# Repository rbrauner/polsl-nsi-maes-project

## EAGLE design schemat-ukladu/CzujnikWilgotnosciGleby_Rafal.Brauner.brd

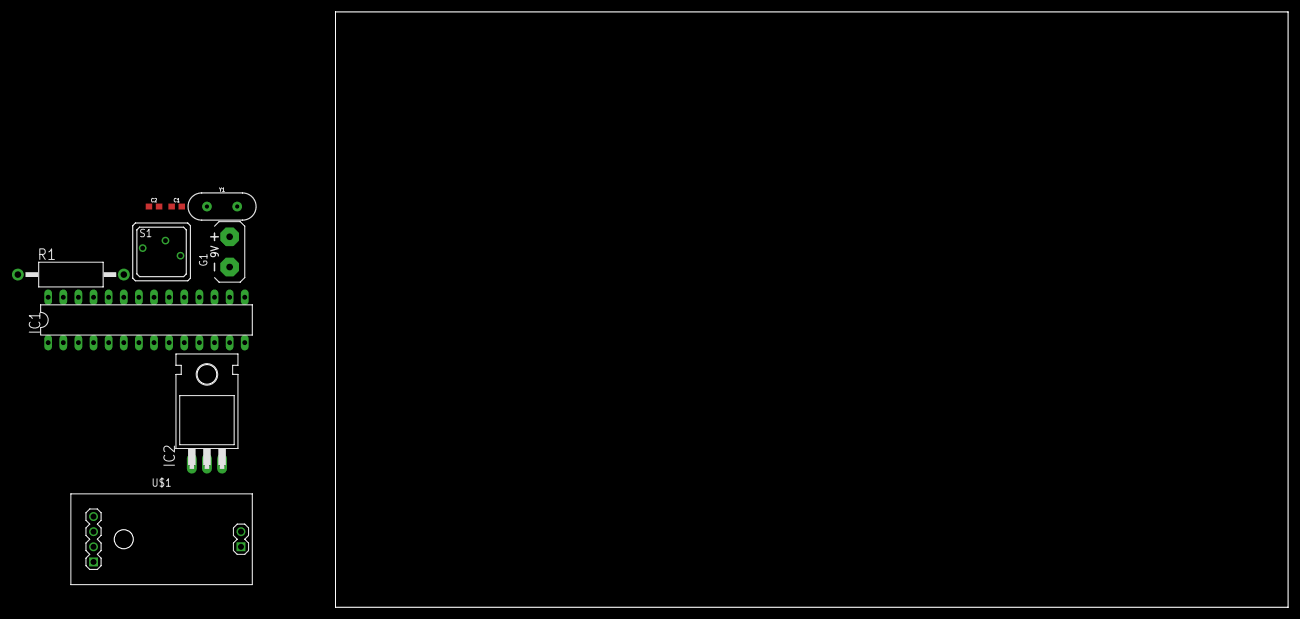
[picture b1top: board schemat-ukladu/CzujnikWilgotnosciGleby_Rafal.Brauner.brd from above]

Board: 2 copper layers, 160.0 x 100.0 mm, 9 parts (0 on the bottom side), 8 nets, no tracks yet.

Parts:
C1, C2: 100pF; 0603
G1: AB9V
IC1: ATMEGA328-20P; DIL28-3
IC2: LM1117T(H)-5.0; TO220H
R1: 100k; AC01
S1: RDT1034
U$1: SOIL-MOISTURE-SENSOR
Y1: HC49US

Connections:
unnamed: G1.+, IC2.3
unnamed: C1.2, IC1.7, IC1.20, IC2.2, R1.2, U$1.J1.4
unnamed: IC1.1, S1.A1
unnamed: R1.1, S1.B
unnamed: C1.1, IC1.9, Y1.2
unnamed: C2.2, G1.-, IC1.8, IC1.22, IC2.1, U$1.J1.3
unnamed: C2.1, IC1.10, Y1.1
unnamed: IC1.28, U$1.J1.1

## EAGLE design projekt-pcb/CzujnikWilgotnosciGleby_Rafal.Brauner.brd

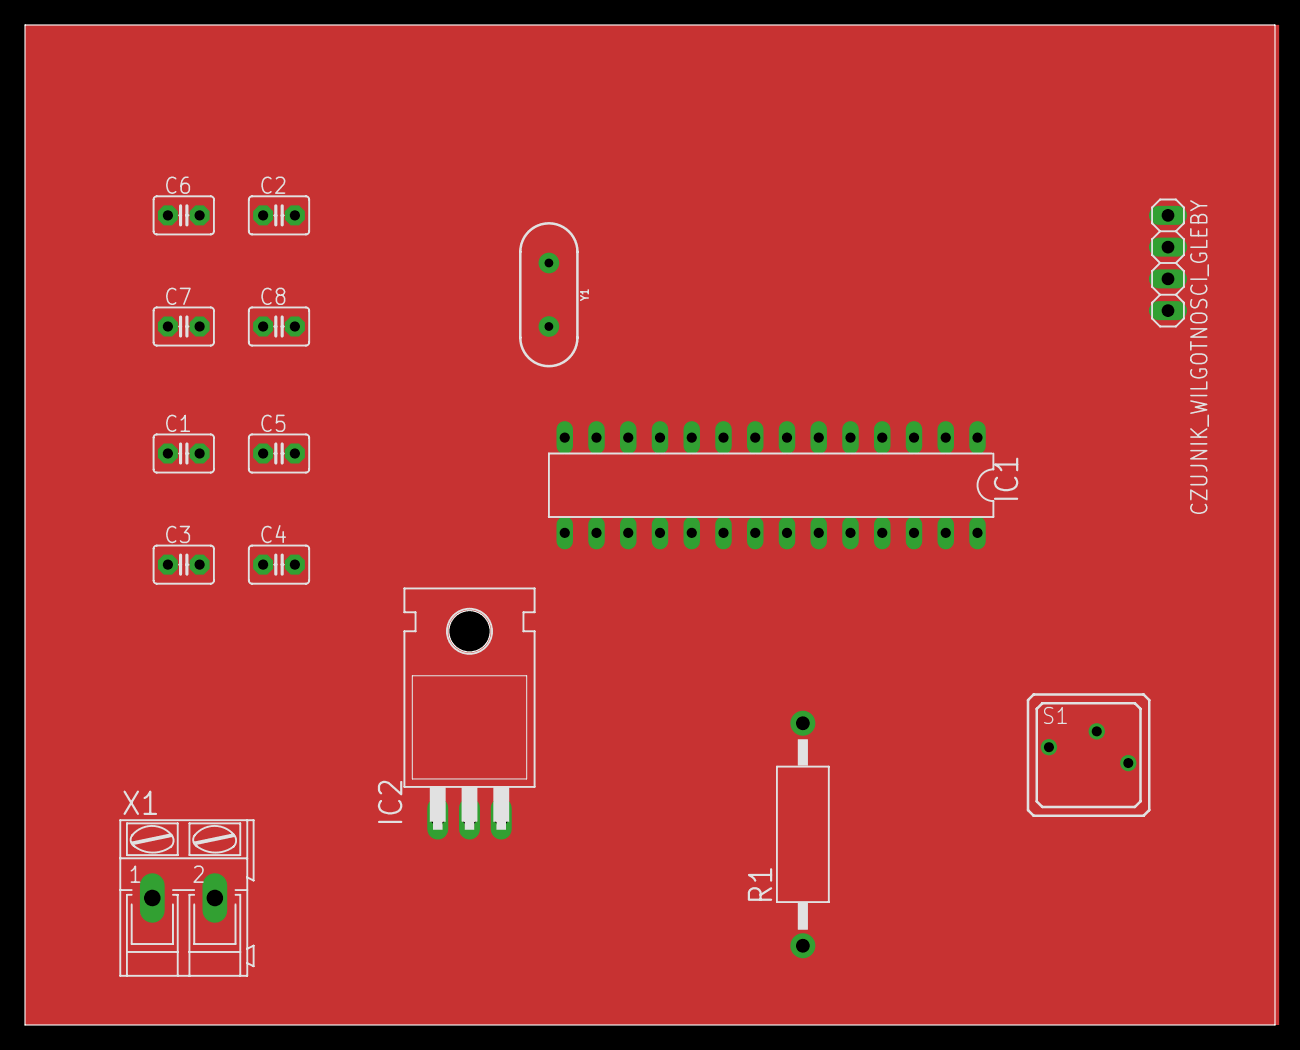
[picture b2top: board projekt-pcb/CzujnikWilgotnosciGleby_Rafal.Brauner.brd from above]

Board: 2 copper layers, 100.0 x 80.0 mm, 15 parts (0 on the bottom side), 9 nets.

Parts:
C1, C2, C3, C4, C6, C7, C8: 100nF; C2.5-3
C5: 22nF; C2.5-3
CZUJNIK_WILGOTNOSCI_GLEBY: 1X04
IC1: ATMEGA328-20P; DIL28-3
IC2: LM1117T(H)-5.0; TO220H
R1: 100k; AC01
S1: RDT1034
X1: AK300/2
Y1: HC49US

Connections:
unnamed: C3.1, IC2.3, X1.1
unnamed: C4.1, C5.1, C6.2, C7.2, CZUJNIK_WILGOTNOSCI_GLEBY.1, IC1.7, IC1.20, IC2.2, R1.2
unnamed: C1.1, C2.1, C3.2, C4.2, C5.2, C6.1, C7.1, C8.2, CZUJNIK_WILGOTNOSCI_GLEBY.2, IC1.8, IC1.22, IC2.1, X1.2
unnamed: IC1.1, S1.A1
unnamed: R1.1, S1.B
unnamed: C1.2, IC1.9, Y1.2
unnamed: C8.1, IC1.21
unnamed: C2.2, IC1.10, Y1.1
unnamed: CZUJNIK_WILGOTNOSCI_GLEBY.4, IC1.28

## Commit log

2021-09-01 Add LICENSE
2021-09-18 project

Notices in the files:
parts and their libraries:
SparkFun-Clocks: Licensing: Creative Commons ShareAlike 4.0 International - https://creativecommons.org/licenses/by-sa/4.0
diy-modules: Released under the Creative Commons Attribution 4.0 International License: http://creativecommons.org/licenses/by/4.0
